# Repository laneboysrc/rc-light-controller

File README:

This project is for a light controller for Radio Controlled cars. 

See http://laneboysrc.blogspot.sg/2012/07/diy-car-light-controller-for-3-channel.html
for details.

It makes uses of a PIC 16F628A microcontroller. Firmware and schematics in
Eagle format are included.

To compile you need:
- GNU Make
- gputils (Version 1.0.0; http://gputils.sourceforge.net/)

Also heck out http://laneboysrc.blogspot.sg/2012/12/pre-processor-for-diy-rc-light.html

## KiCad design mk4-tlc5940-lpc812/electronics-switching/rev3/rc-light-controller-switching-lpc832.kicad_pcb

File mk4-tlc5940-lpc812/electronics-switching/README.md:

# Mk4S - light controller with pin headers and 9 switching outputs

This is a new variant of the DIY RC Light Controller Mk4.
It has 9 (Mosfet) switched outputs on standard 2.54 mm pin headers, 8 of them with two connections and one of them with 1 connection.

We are using the TSSOP-20 package of the LPC812 as it is easier to source (as of 2020) than the TSSOP-16 version, and we have plenty of space.

# 2021 electronics shortage

As of early 2021, many electronics components are out of stock due to global semiconductor shortage. This affects also the LPC812 microcontroller.

As of April 2021 a similar microcontroller from NXP, the LPC832M101FDH20 was still in stock at some distributors (but stocks declined towards mid of April rapidly). We prepared a new circuit board for the LPC832, and also ported the firmware.

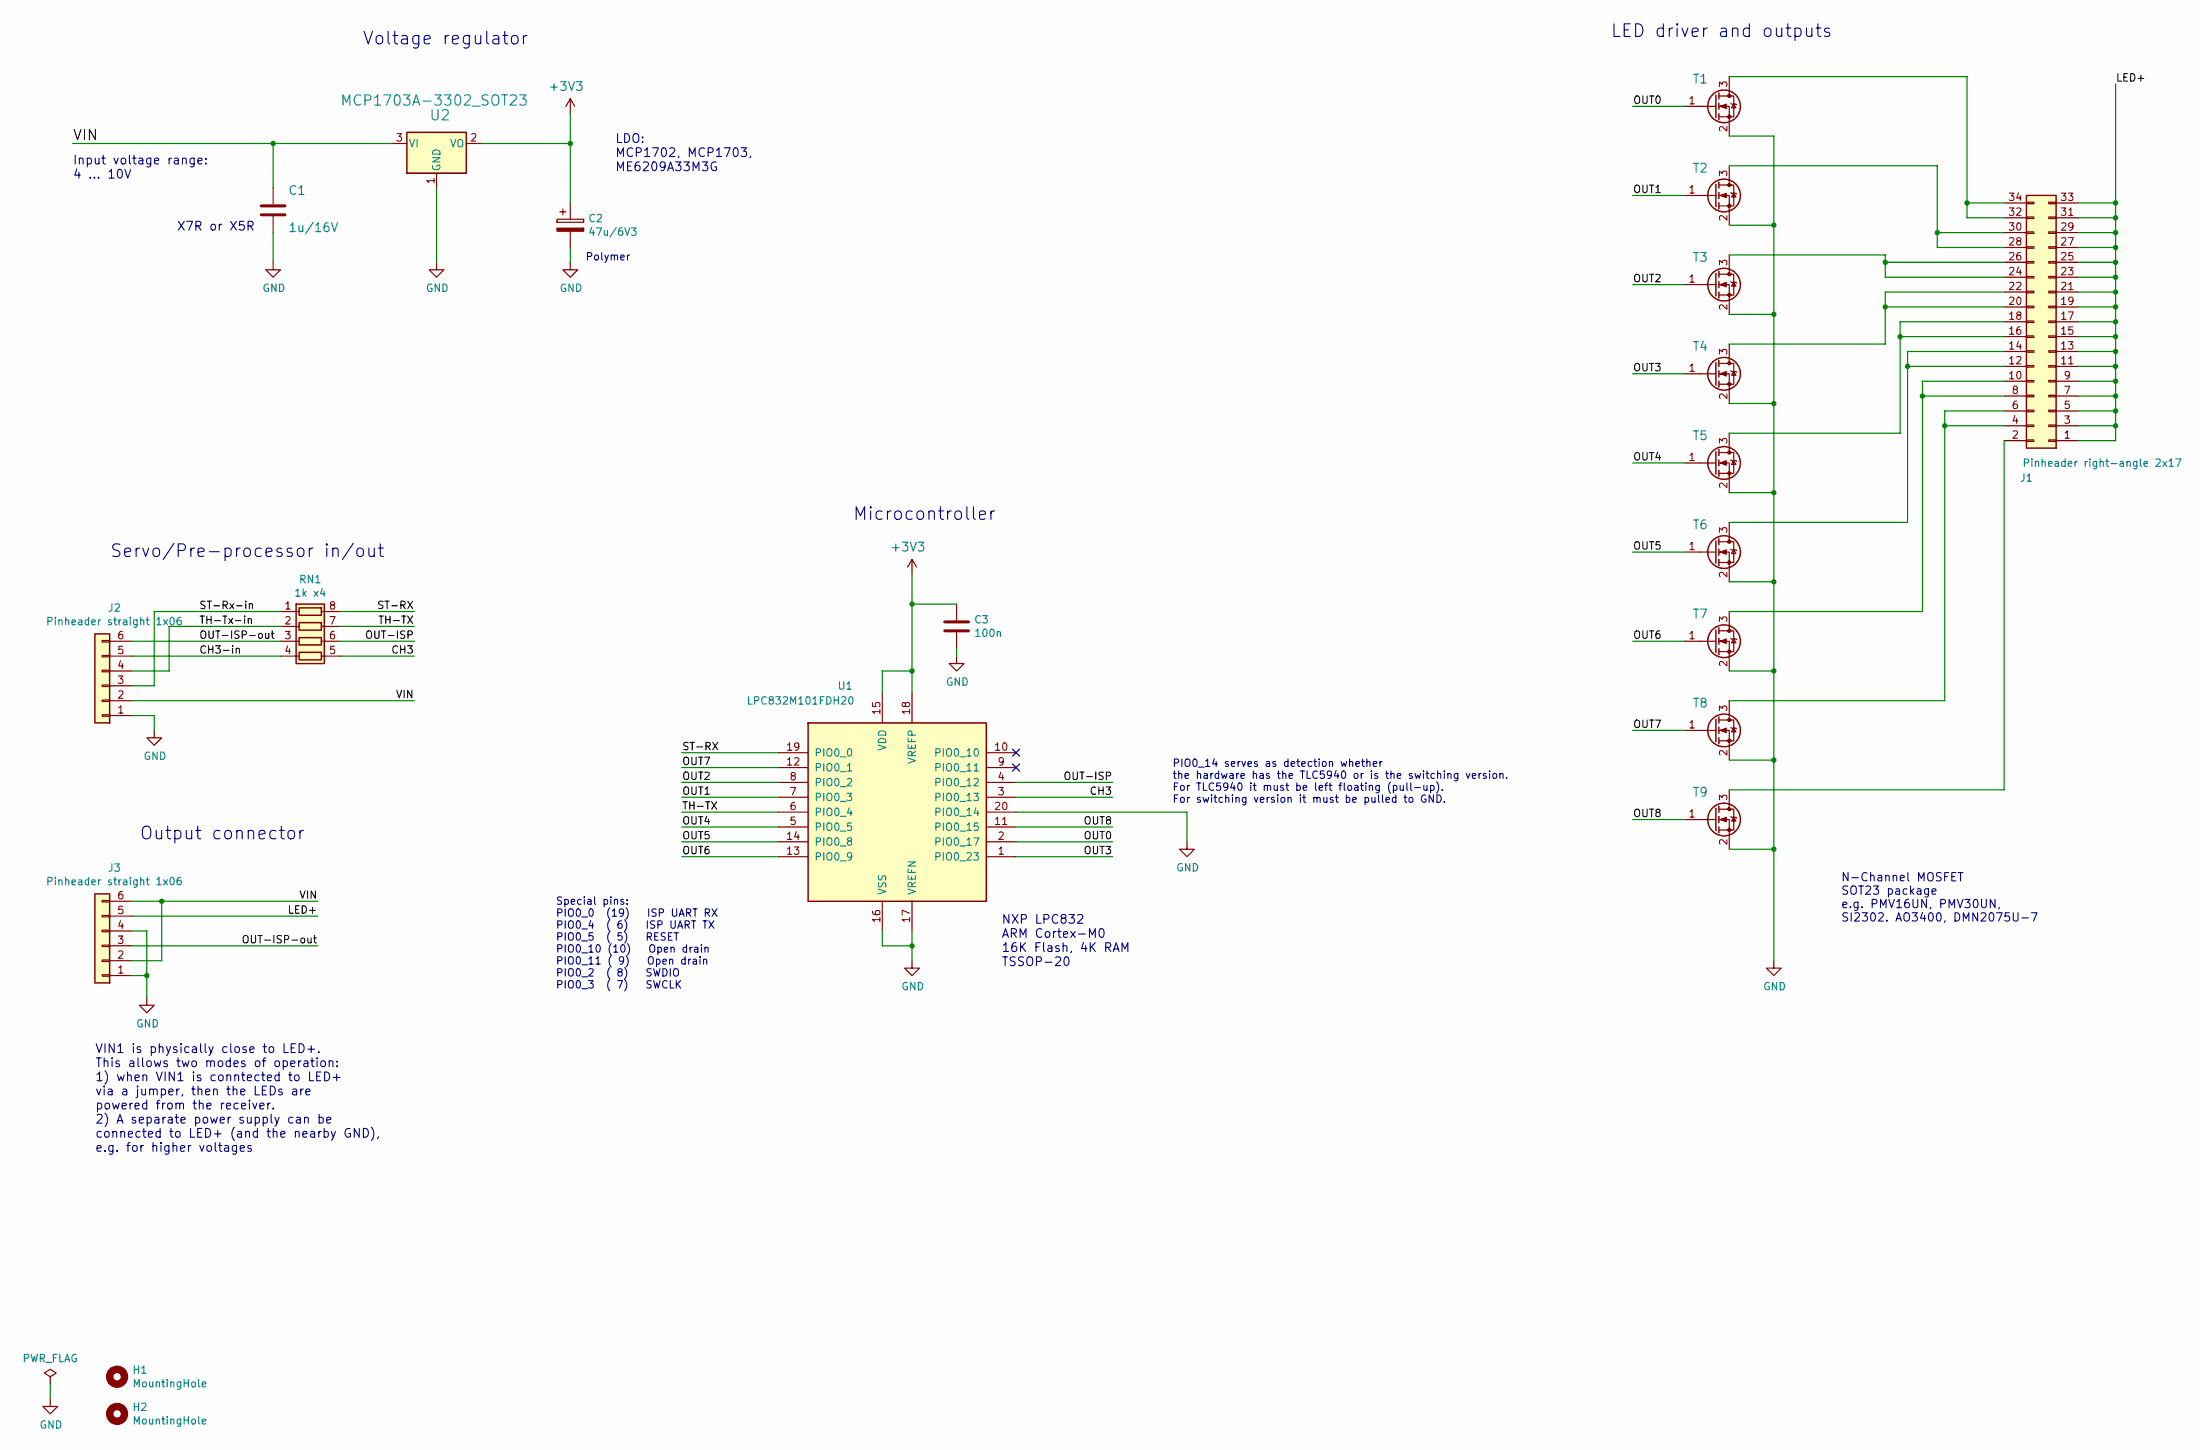
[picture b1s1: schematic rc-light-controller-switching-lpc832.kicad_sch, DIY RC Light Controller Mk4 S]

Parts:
C1: 1u/16V; C_0805_2012Metric
C2: 47u/6V3; C_0805_2012Metric
C3: 100n; C_0603_1608Metric
H1, H2: MountingHole; MountingHole_2.2mm_M2_ISO14580
J1: Pinheader right-angle 2x17; PinHeader_2x17_P2.54mm_Horizontal
J2, J3: Pinheader straight 1x06; PinHeader_1x06_P2.54mm_Flat
RN1: 1k x4; R_Array_Convex_4x0603
T1, T2, T3, T4, T5, T6, T7, T8, T9: PMV30UN; SOT-23
U1: LPC832M101FDH20; TSSOP-20_4.4x6.5mm_P0.65mm
U2: MCP1703A-3302_SOT23; SOT-23W

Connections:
+3V3: C2.1, C3.1, U1.15 (VDD), U1.18 (VREFP), U2.2 (VO)
/CH3: RN1.5 (R4.2), U1.3 (PIO0_13)
/CH3-in: J2.5, RN1.4 (R4.1)
/LED+: J1.1, J1.3, J1.5, J1.7, J1.9, J1.11, J1.13, J1.15, J1.17, J1.19, J1.21, J1.23, J1.25, J1.27, J1.29, J1.31, J1.33, J3.5
/OUT0: T1.1 (G), U1.2 (PIO0_17)
/OUT1: T2.1 (G), U1.7 (PIO0_3)
/OUT2: T3.1 (G), U1.8 (PIO0_2)
/OUT3: T4.1 (G), U1.1 (PIO0_23)
/OUT4: T5.1 (G), U1.5 (PIO0_5)
/OUT5: T6.1 (G), U1.14 (PIO0_8)
/OUT6: T7.1 (G), U1.13 (PIO0_9)
/OUT7: T8.1 (G), U1.12 (PIO0_1)
/OUT8: T9.1 (G), U1.11 (PIO0_15)
/OUT-ISP: RN1.6 (R3.2), U1.4 (PIO0_12)
/OUT-ISP-out: J2.6, J3.3, RN1.3 (R3.1)
/ST-RX: RN1.8 (R1.2), U1.19 (PIO0_0)
/ST-Rx-in: J2.3, RN1.1 (R1.1)
/TH-TX: RN1.7 (R2.2), U1.6 (PIO0_4)
/TH-Tx-in: J2.4, RN1.2 (R2.1)
/VIN: C1.1, J2.2, J3.2, J3.6, U2.3 (VI)
GND: C1.2, C2.2, C3.2, J2.1, J3.1, J3.4, T1.2 (S), T2.2 (S), T3.2 (S), T4.2 (S), T5.2 (S), T6.2 (S), T7.2 (S), T8.2 (S), T9.2 (S), U1.16 (VSS), U1.17 (VREFN), U1.20 (PIO0_14), U2.1 (GND)
unnamed: J1.2, T9.3 (D)
unnamed: J1.4, J1.6, T8.3 (D)
unnamed: J1.8, J1.10, T7.3 (D)
unnamed: J1.12, J1.14, T6.3 (D)
unnamed: J1.16, J1.18, T5.3 (D)
unnamed: J1.20, J1.22, T4.3 (D)
unnamed: J1.24, J1.26, T3.3 (D)
unnamed: J1.28, J1.30, T2.3 (D)
unnamed: J1.32, J1.34, T1.3 (D)

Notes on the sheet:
N-Channel MOSFET SOT23 package e.g. PMV16UN, PMV30UN, SI2302. AO3400, DMN2075U-7
PIO0_14 serves as detection whether the hardware has the TLC5940 or is the switching version. For TLC5940 it must be left floating (pull-up). For switching version it must be pulled to GND.
Polymer
Microcontroller
X7R or X5R
Input voltage range: 4 ... 10V
LED driver and outputs
Special pins: PIO0_0 (19) ISP UART RX PIO0_4 ( 6) ISP UART TX PIO0_5 ( 5) RESET PIO0_10 (10) Open drain PIO0_11 ( 9) Open drain PIO0_2 ( 8) SWDIO PIO0_3 ( 7) SWCLK
Servo/Pre-processor in/out
Voltage regulator
VIN1 is physically close to LED+. This allows two modes of operation: 1) when VIN1 is conntected to LED+ via a jumper, then the LEDs are powered from the receiver. 2) A separate power supply can be connected to LED+ (and the nearby GND), e.g. for higher voltages
LDO: MCP1702, MCP1703, ME6209A33M3G
Output connector
NXP LPC832 ARM Cortex-M0 16K Flash, 4K RAM TSSOP-20

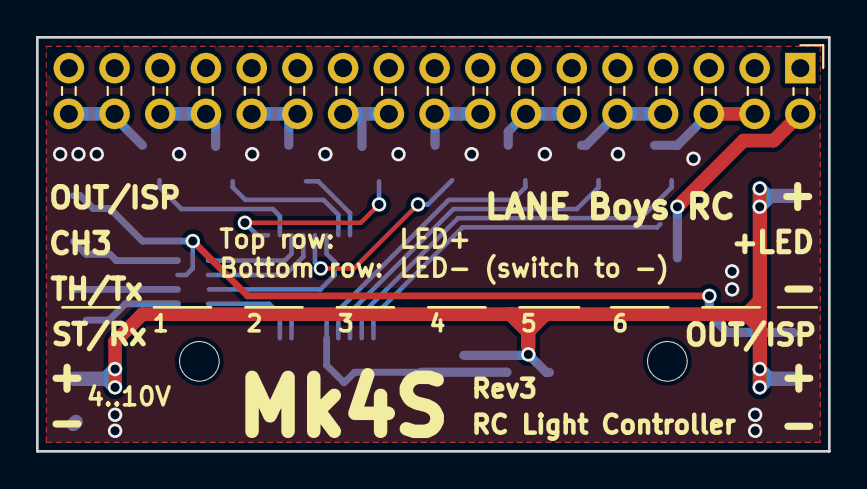
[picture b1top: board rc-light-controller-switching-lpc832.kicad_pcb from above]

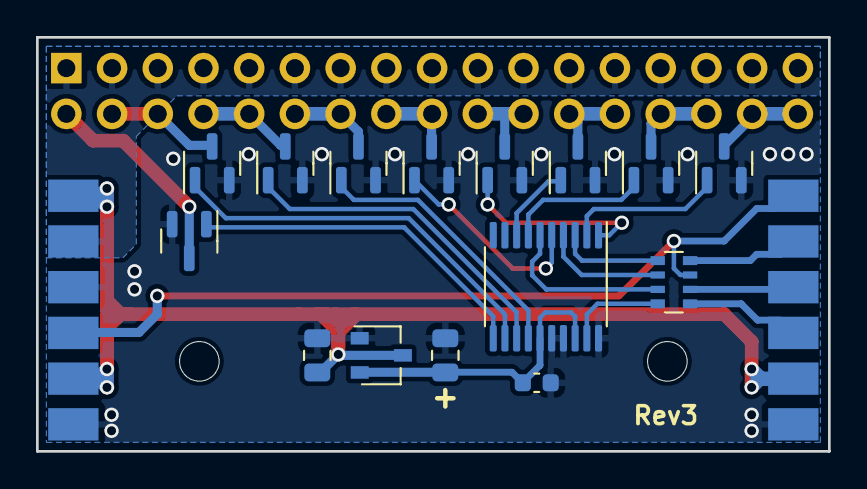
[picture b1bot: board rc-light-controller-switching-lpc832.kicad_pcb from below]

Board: 2 copper layers, 44.0 x 23.0 mm, 20 parts (17 on the bottom side), 30 nets.

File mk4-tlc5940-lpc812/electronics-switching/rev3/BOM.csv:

Reference, Quantity, Value, Footprint, Datasheet
C1 ,1,"1u/16V","Capacitor_SMD:C_0805_2012Metric",""
C2 ,1,"47u/6V3","Capacitor_SMD:C_0805_2012Metric","https://www.vishay.com/doc?40189"
C3 ,1,"100n","Capacitor_SMD:C_0603_1608Metric","~"
H1 H2 ,2,"MountingHole","MountingHole:MountingHole_2.2mm_M2_ISO14580","~"
J1 ,1,"Pinheader right-angle 2x17","Connector_PinHeader_2.54mm:PinHeader_2x17_P2.54mm_Horizontal","~"
J2 J3 ,2,"Pinheader straight 1x06","rc-light-controller-tlc5940-lpc812:PinHeader_1x06_P2.54mm_Flat","~"
RN1 ,1,"1k x4","Resistor_SMD:R_Array_Convex_4x0603","https://datasheet.lcsc.com/szlcsc/1810311812_UNI-ROYAL-Uniro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"
T1 T2 T3 T4 T5 T6 T7 T9 T8 ,9,"PMV30UN","Package_TO_SOT_SMD:SOT-23","https://assets.nexperia.com/documents/data-sheet/PMV30UN.pdf"
U1 ,1,"LPC832M101FDH20","Package_SO:TSSOP-20_4.4x6.5mm_P0.65mm","http://www.nxp.com/documents/data_sheet/LPC83X.pdf"
U2 ,1,"MCP1703A-3302","Package_TO_SOT_SMD:SOT-23W",""

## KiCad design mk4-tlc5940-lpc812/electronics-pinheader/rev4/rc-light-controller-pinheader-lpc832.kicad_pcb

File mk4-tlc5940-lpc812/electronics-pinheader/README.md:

# Mk4P - light controller with pin headers

This is a variant of the DIY RC Light Controller Mk4 where all outputs are available on a standard 2.54 mm pin header.

We are using a microcontroller from NXP: LPC824M101FDH20 (or LPC832M101FDH20) in TSSOP-20 package.

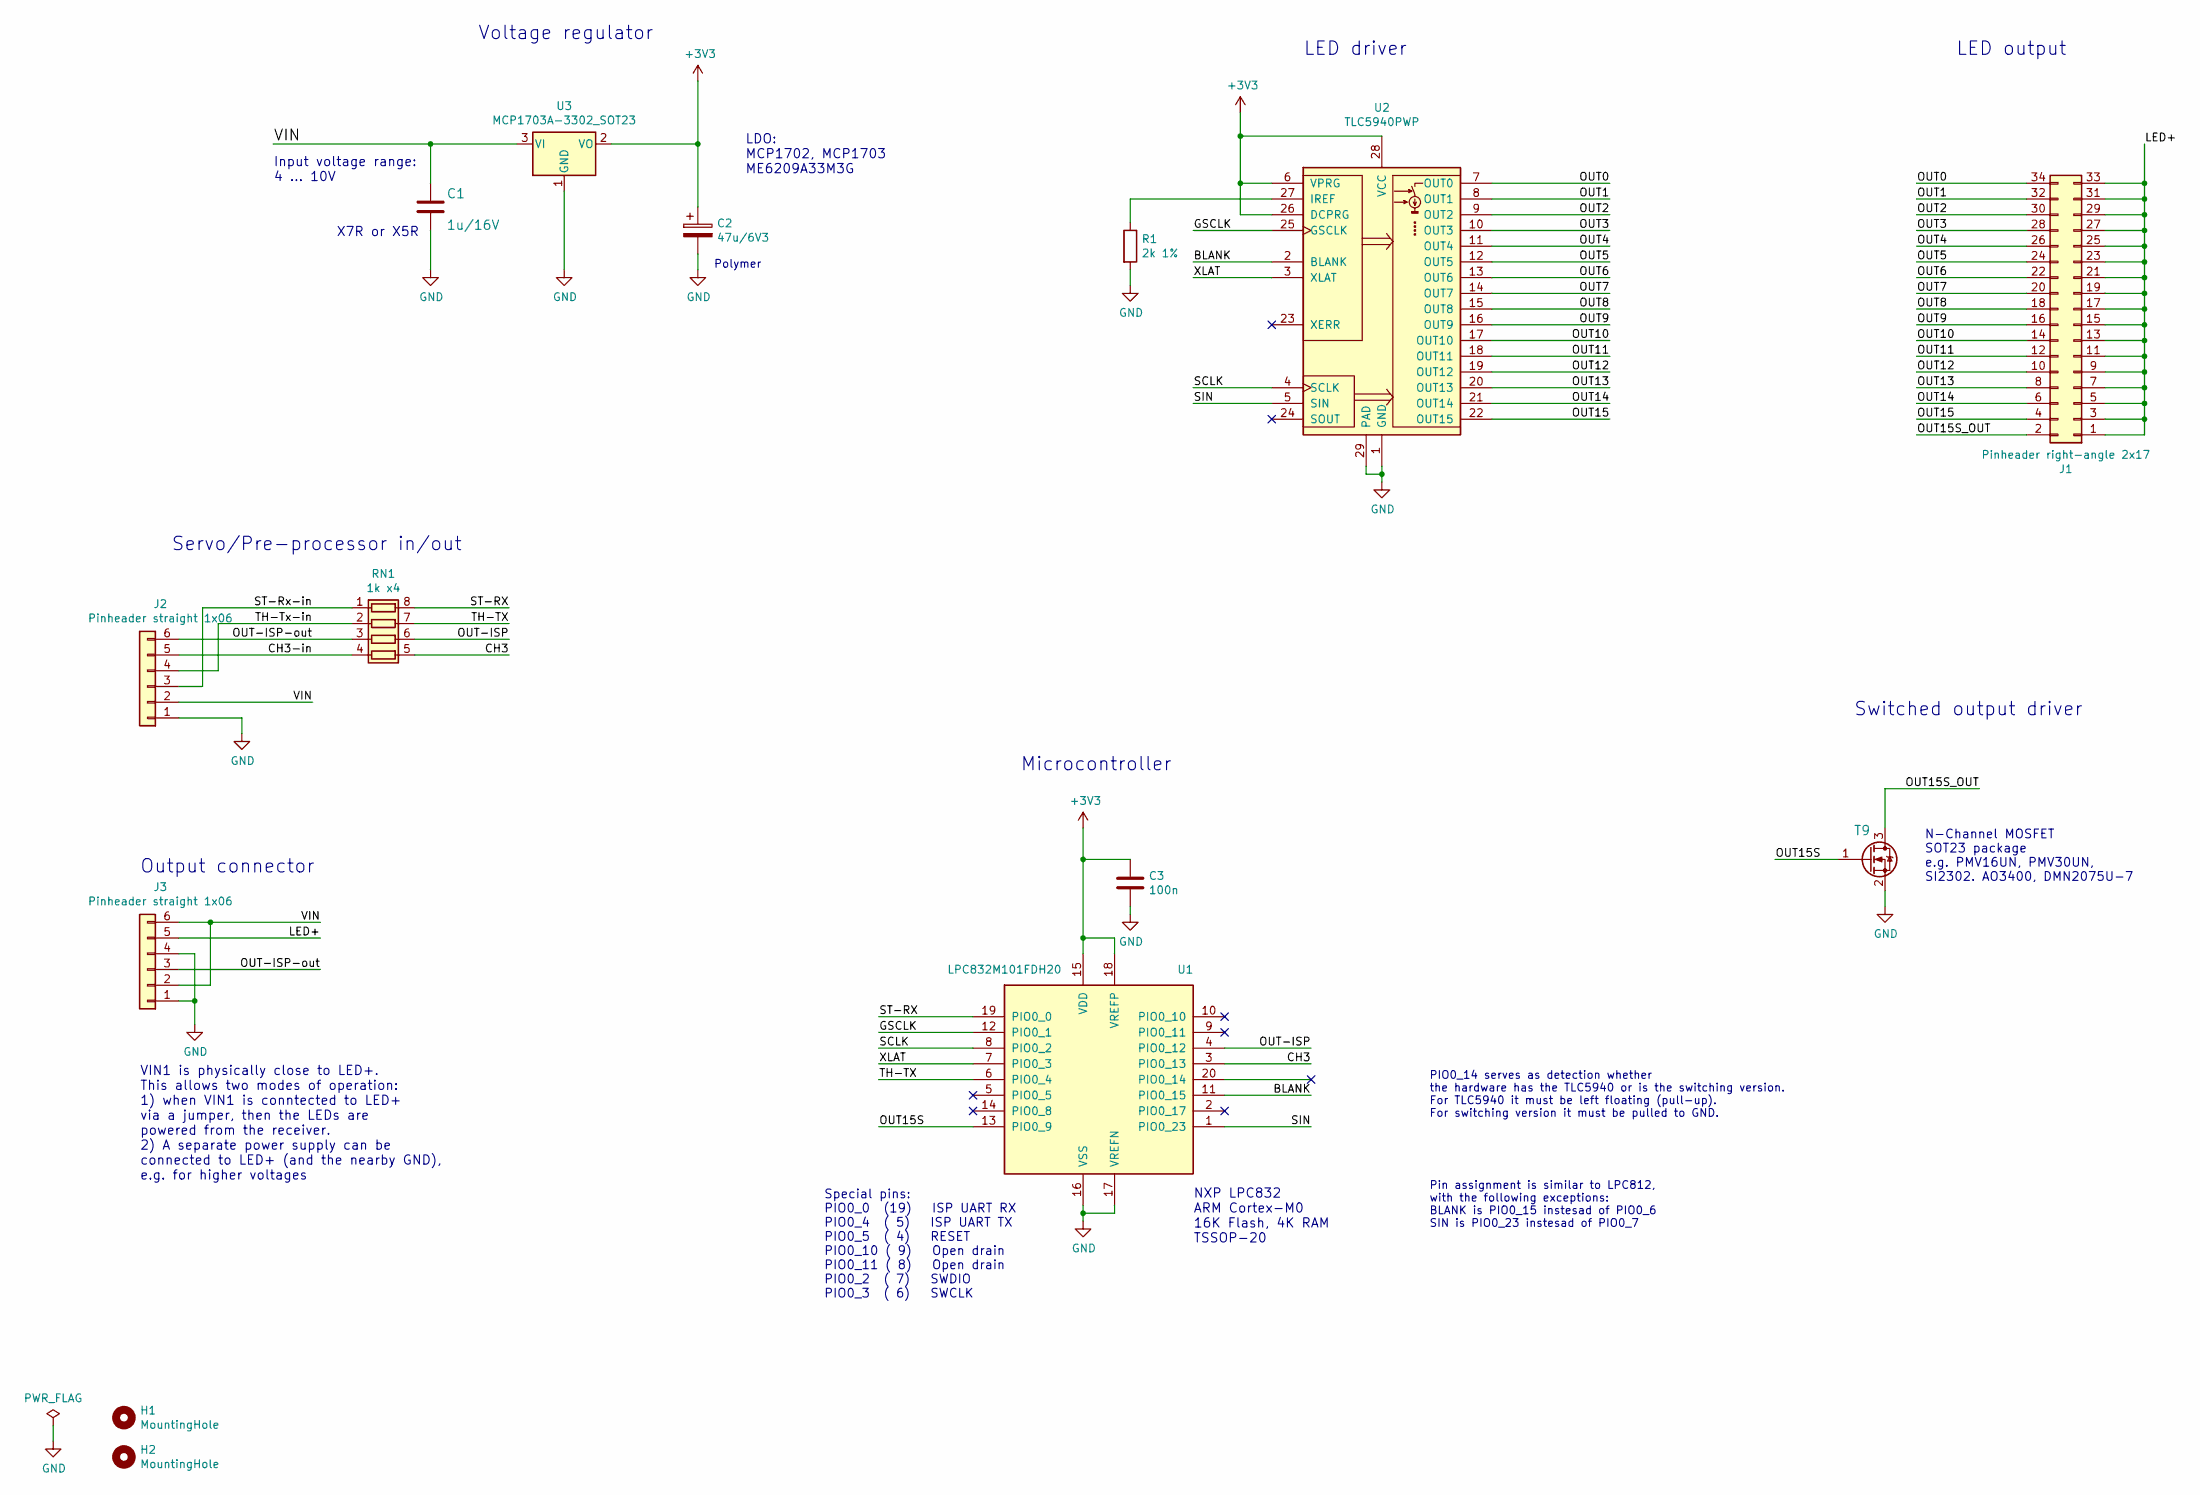
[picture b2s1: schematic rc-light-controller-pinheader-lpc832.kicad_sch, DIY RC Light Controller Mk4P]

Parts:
C1: 1u/16V; C_0805_2012Metric
C2: 47u/6V3; C_0805_2012Metric
C3: 100n; C_0603_1608Metric
H1, H2: MountingHole; MountingHole_2.2mm_M2_ISO14580
J1: Pinheader right-angle 2x17; PinHeader_2x17_P2.54mm_Horizontal
J2, J3: Pinheader straight 1x06; PinHeader_1x06_P2.54mm_Flat
R1: 2k 1%; R_0603_1608Metric
RN1: 1k x4; R_Array_Convex_4x0603
T9: PMV30UN; SOT-23
U1: LPC832M101FDH20; TSSOP-20_4.4x6.5mm_P0.65mm
U2: TLC5940PWP; SOP65P640X120-29N
U3: MCP1703A-3302_SOT23; SOT-23W

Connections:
+3V3: C2.1, C3.1, U1.15 (VDD), U1.18 (VREFP), U2.6 (VPRG), U2.26 (DCPRG), U2.28 (VCC), U3.2 (VO)
/BLANK: U1.11 (PIO0_15), U2.2 (BLANK)
/CH3: RN1.5 (R4.2), U1.3 (PIO0_13)
/CH3-in: J2.5, RN1.4 (R4.1)
/GSCLK: U1.12 (PIO0_1), U2.25 (GSCLK)
/LED+: J1.1, J1.3, J1.5, J1.7, J1.9, J1.11, J1.13, J1.15, J1.17, J1.19, J1.21, J1.23, J1.25, J1.27, J1.29, J1.31, J1.33, J3.5
/OUT0: J1.34, U2.7 (OUT0)
/OUT1: J1.32, U2.8 (OUT1)
/OUT2: J1.30, U2.9 (OUT2)
/OUT3: J1.28, U2.10 (OUT3)
/OUT4: J1.26, U2.11 (OUT4)
/OUT5: J1.24, U2.12 (OUT5)
/OUT6: J1.22, U2.13 (OUT6)
/OUT7: J1.20, U2.14 (OUT7)
/OUT8: J1.18, U2.15 (OUT8)
/OUT9: J1.16, U2.16 (OUT9)
/OUT10: J1.14, U2.17 (OUT10)
/OUT11: J1.12, U2.18 (OUT11)
/OUT12: J1.10, U2.19 (OUT12)
/OUT13: J1.8, U2.20 (OUT13)
/OUT14: J1.6, U2.21 (OUT14)
/OUT15: J1.4, U2.22 (OUT15)
/OUT15S: T9.1 (G), U1.13 (PIO0_9)
/OUT15S_OUT: J1.2, T9.3 (D)
/OUT-ISP: RN1.6 (R3.2), U1.4 (PIO0_12)
/OUT-ISP-out: J2.6, J3.3, RN1.3 (R3.1)
/SCLK: U1.8 (PIO0_2), U2.4 (SCLK)
/SIN: U1.1 (PIO0_23), U2.5 (SIN)
/ST-RX: RN1.8 (R1.2), U1.19 (PIO0_0)
/ST-Rx-in: J2.3, RN1.1 (R1.1)
/TH-TX: RN1.7 (R2.2), U1.6 (PIO0_4)
/TH-Tx-in: J2.4, RN1.2 (R2.1)
/VIN: C1.1, J2.2, J3.2, J3.6, U3.3 (VI)
/XLAT: U1.7 (PIO0_3), U2.3 (XLAT)
GND: C1.2, C2.2, C3.2, J2.1, J3.1, J3.4, R1.2, T9.2 (S), U1.16 (VSS), U1.17 (VREFN), U2.1 (GND), U2.29 (PAD), U3.1 (GND)
unnamed: R1.1, U2.27 (IREF)

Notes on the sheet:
N-Channel MOSFET SOT23 package e.g. PMV16UN, PMV30UN, SI2302. AO3400, DMN2075U-7
LED driver
Microcontroller
LED output
Special pins: PIO0_0 (19) ISP UART RX PIO0_4 ( 5) ISP UART TX PIO0_5 ( 4) RESET PIO0_10 ( 9) Open drain PIO0_11 ( 8) Open drain PIO0_2 ( 7) SWDIO PIO0_3 ( 6) SWCLK
LDO: MCP1702, MCP1703 ME6209A33M3G
X7R or X5R
PIO0_14 serves as detection whether the hardware has the TLC5940 or is the switching version. For TLC5940 it must be left floating (pull-up). For switching version it must be pulled to GND.
Polymer
Pin assignment is similar to LPC812, with the following exceptions: BLANK is PIO0_15 instesad of PIO0_6 SIN is PIO0_23 instesad of PIO0_7
VIN1 is physically close to LED+. This allows two modes of operation: 1) when VIN1 is conntected to LED+ via a jumper, then the LEDs are powered from the receiver. 2) A separate power supply can be connected to LED+ (and the nearby GND), e.g. for higher voltages
Voltage regulator
Servo/Pre-processor in/out
Switched output driver
NXP LPC832 ARM Cortex-M0 16K Flash, 4K RAM TSSOP-20
Output connector
Input voltage range: 4 ... 10V

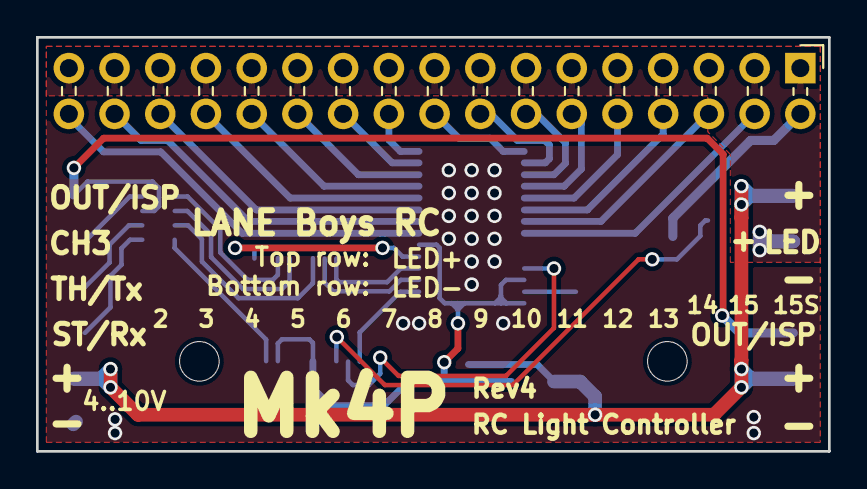
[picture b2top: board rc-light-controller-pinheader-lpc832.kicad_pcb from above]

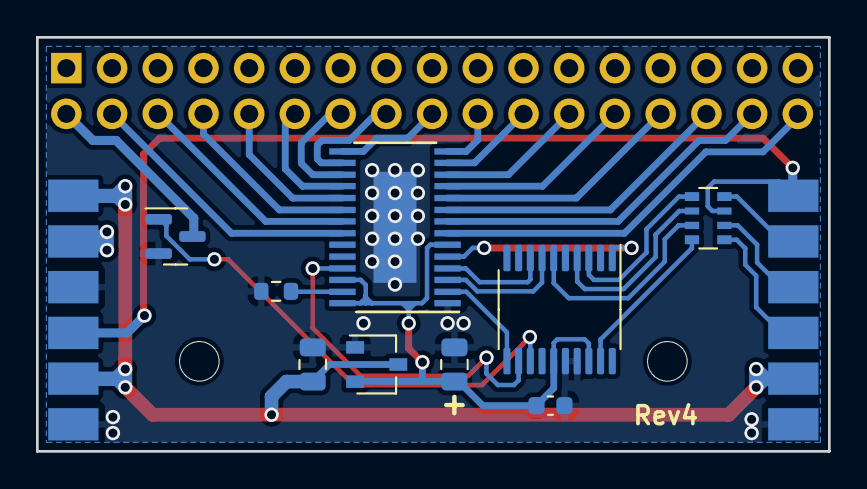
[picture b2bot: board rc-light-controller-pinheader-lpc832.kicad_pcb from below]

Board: 2 copper layers, 44.0 x 23.0 mm, 14 parts (11 on the bottom side), 36 nets.

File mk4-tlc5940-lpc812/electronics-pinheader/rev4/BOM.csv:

Reference, Quantity, Value, Footprint, Datasheet
C1 ,1,1u/16V,Capacitor_SMD:C_0805_2012Metric,
C2 ,1,47u/6V3,Capacitor_SMD:C_0805_2012Metric,https://www.vishay.com/doc?40189
C3 ,1,100n,Capacitor_SMD:C_0603_1608Metric,~
H1 H2 ,2,MountingHole,MountingHole:MountingHole_2.2mm_M2_ISO14580,~
J1 ,1,Pinheader right-angle 2x17,Connector_PinHeader_2.54mm:PinHeader_2x17_P2.54mm_Horizontal,~
J2 J3 ,2,Pinheader straight 1x06,rc-light-controller-tlc5940-lpc812:PinHeader_1x06_P2.54mm_Flat,~
R1 ,1,2k 1%,Resistor_SMD:R_0603_1608Metric,~
RN1 ,1,1k x4,Resistor_SMD:R_Array_Convex_4x0603,https://datasheet.lcsc.com/szlcsc/1810311812_UNI-ROYAL-Uniro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
T9 ,1,PMV30UN,Package_TO_SOT_SMD:SOT-23,https://assets.nexperia.com/documents/data-sheet/PMV30UN.pdf
U1 ,1,LPC832M101FDH20,Package_SO:TSSOP-20_4.4x6.5mm_P0.65mm,http://www.nxp.com/documents/data_sheet/LPC81XM.pdf
U2 ,1,TLC5940PWPR,rc-light-controller-tlc5940-lpc812:SOP65P640X120-29N,http://www.ti.com/lit/ds/symlink/tlc5940.pdf
U3 ,1,MCP1703A-3302_SOT23,Package_TO_SOT_SMD:SOT-23W,http://ww1.microchip.com/downloads/en/DeviceDoc/20005122B.pdf

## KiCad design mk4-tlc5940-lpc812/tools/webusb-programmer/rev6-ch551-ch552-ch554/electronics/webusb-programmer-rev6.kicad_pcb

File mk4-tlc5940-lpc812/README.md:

# Light controller MK4 TLC5940 LPC812 / LPC832

Usually light controller users can use the on-line Configurator at https://laneboysrc.github.io/rc-light-controller/ to adjust all settings to their need and use the WebUSB programmer to flash the resulting firmware.

---

For configuring the light controller offline, please download **[mk4-download-me.zip](mk4-download-me.zip)**.

This archive contains the configuration tool *configurator.html*. Open this file in your Web browser.
**configurator.html has the firmware already embedded**, just set the options you want and click on the *Save firmware image...* button.

The configured firmware image *light_controller.hex* will be stored in the *Download* folder of your web browser.

If you don't have the WebUSB programmer, you can use the LPC81x-ISP tool included in the archive to flash the firmware. You need a USB-to-serial adapter to connect your PC to the light controller.

Wire-up the USB-to-serial adapter as follows:

---

In the rare event you want to modify the firmware, please consult [README.md](firmware/README.md) for build instructions.

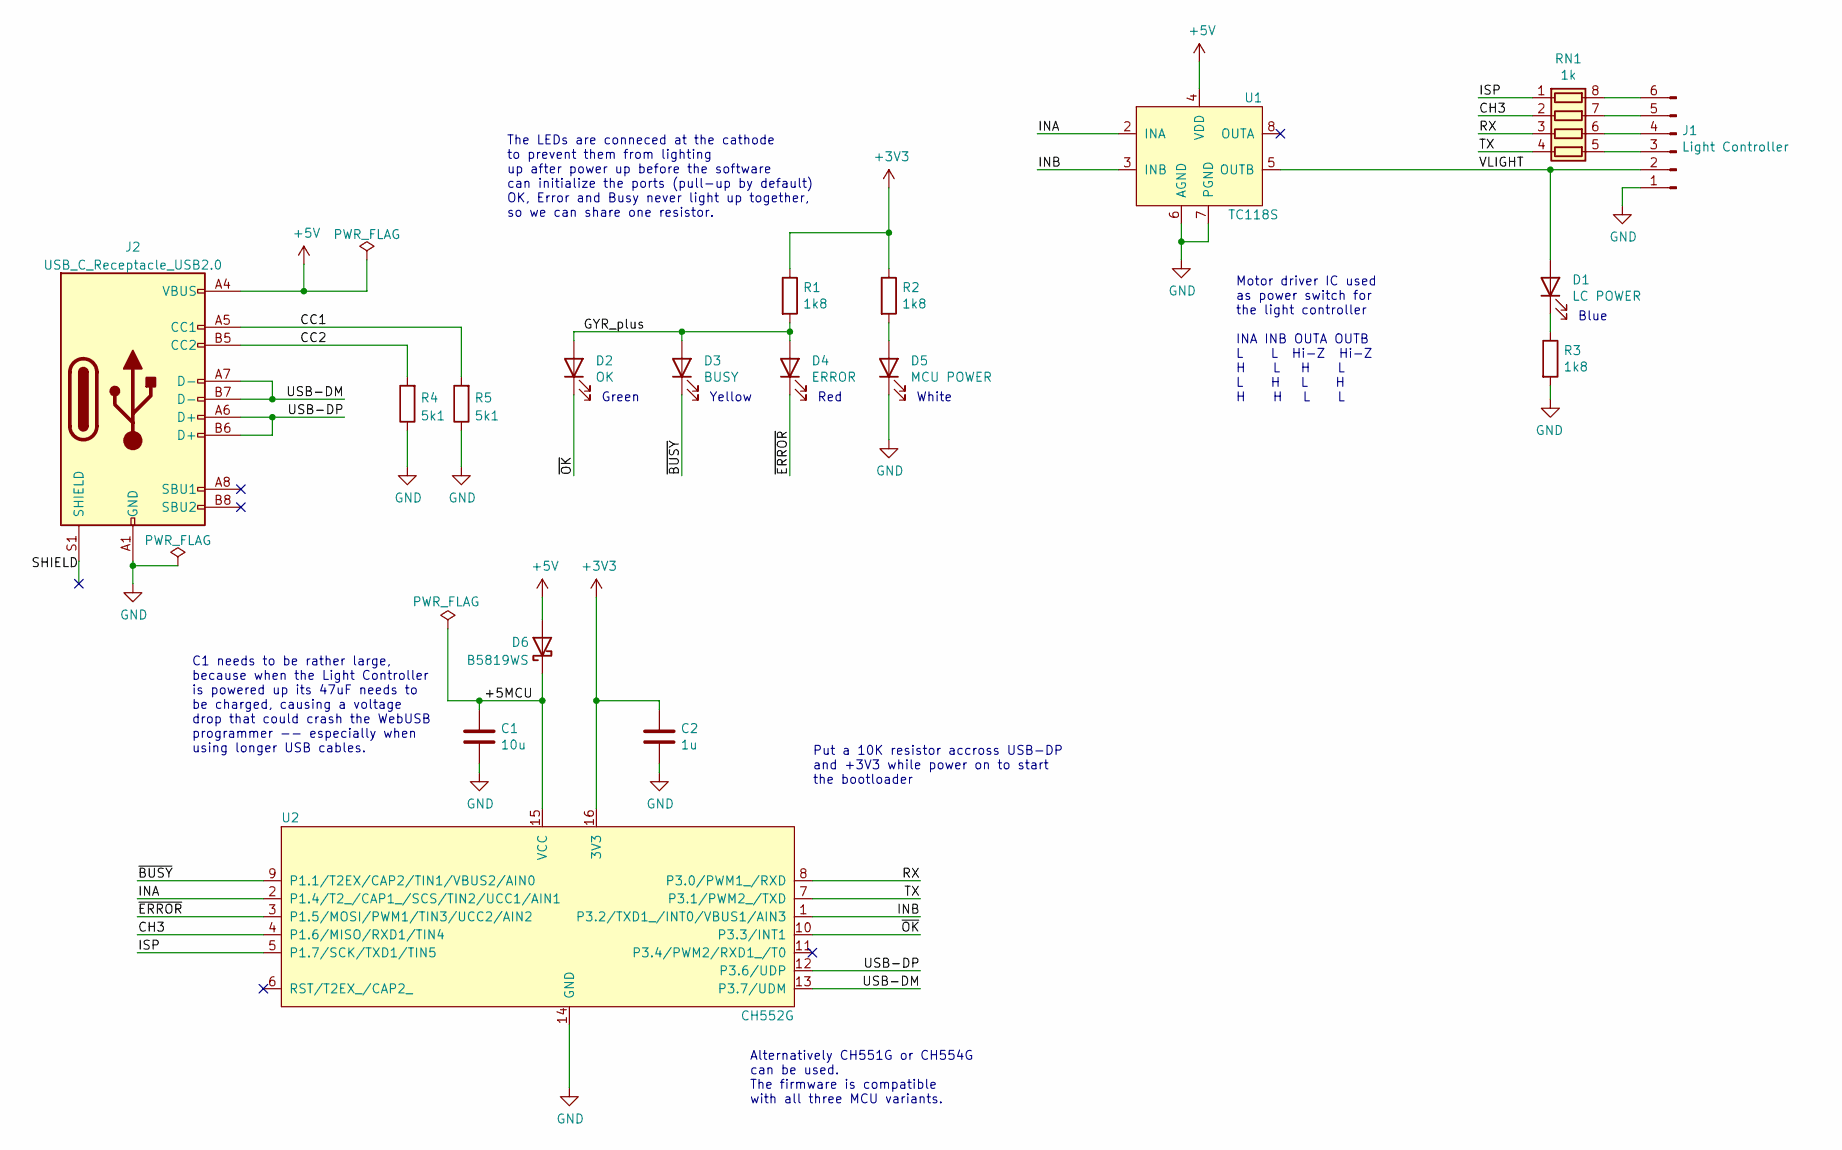
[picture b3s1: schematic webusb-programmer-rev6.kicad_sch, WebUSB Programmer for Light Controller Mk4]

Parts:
C1: 10u; C_0603_1608Metric
C2: 1u; C_0603_1608Metric
D1: LC POWER; LED_0805_2012Metric_see_through; LCSC part number C779807
D2: OK; LED_0805_2012Metric_see_through; LCSC part number C779806
D3: BUSY; LED_0805_2012Metric_see_through; LCSC part number C779805
D4: ERROR; LED_0805_2012Metric_see_through; LCSC part number C389527
D5: MCU POWER; LED_0805_2012Metric_see_through; LCSC part number C779804
D6: B5819WS; D_SOD-123
J1: Light Controller; PinHeader_1x06_P2.54mm_Flat
J2: USB_C_Receptacle_USB2.0; USB_C_Receptacle_G-Switch_GT-USB-7010ASV
R1, R2, R3: 1k8; R_0603_1608Metric
R4, R5: 5k1; R_0603_1608Metric
RN1: 1k; R_Array_Convex_4x0603
U1: TC118S; SOP-8_3.9x4.9mm_P1.27mm; LCSC part number C88308
U2: CH552G; SO-16_3.9x9.9mm_P1.27mm; LCSC part number C111292

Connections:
+3V3: C2.1, R1.1, R2.1, U2.16 (3V3)
+5V: D6.2 (A), J2.A4 (VBUS), J2.A9 (VBUS), J2.B4 (VBUS), J2.B9 (VBUS), U1.4 (VDD)
/+5MCU: C1.1, D6.1 (K), U2.15 (VCC)
/CC1: J2.A5 (CC1), R5.2
/CC2: J2.B5 (CC2), R4.2
/CH3: RN1.2 (R2.1), U2.4 (P1.6/MISO/RXD1/TIN4)
/GYR_plus: D2.2 (A), D3.2 (A), D4.2 (A), R1.2
/INA: U1.2 (INA), U2.2 (P1.4/T2_/CAP1_/SCS/TIN2/UCC1/AIN1)
/INB: U1.3 (INB), U2.1 (P3.2/TXD1_/INT0/VBUS1/AIN3)
/ISP: RN1.1 (R1.1), U2.5 (P1.7/SCK/TXD1/TIN5)
/RX: RN1.3 (R3.1), U2.8 (P3.0/PWM1_/RXD)
/SHIELD: J2.S1 (SHIELD)
/TX: RN1.4 (R4.1), U2.7 (P3.1/PWM2_/TXD)
/USB-DM: J2.A7 (D-), J2.B7 (D-), U2.13 (P3.7/UDM)
/USB-DP: J2.A6 (D+), J2.B6 (D+), U2.12 (P3.6/UDP)
/VLIGHT: D1.2 (A), J1.2, U1.5 (OUTB)
/~BUSY: D3.1 (K), U2.9 (P1.1/T2EX/CAP2/TIN1/VBUS2/AIN0)
/~ERROR: D4.1 (K), U2.3 (P1.5/MOSI/PWM1/TIN3/UCC2/AIN2)
/~OK: D2.1 (K), U2.10 (P3.3/INT1)
GND: C1.2, C2.2, D5.1 (K), J1.1, J2.A1 (GND), J2.A12 (GND), J2.B1 (GND), J2.B12 (GND), R3.2, R4.1, R5.1, U1.6 (AGND), U1.7 (PGND), U2.14 (GND)
unnamed: D1.1 (K), R3.1
unnamed: D5.2 (A), R2.2
unnamed: J1.3, RN1.5 (R4.2)
unnamed: J1.4, RN1.6 (R3.2)
unnamed: J1.5, RN1.7 (R2.2)
unnamed: J1.6, RN1.8 (R1.2)

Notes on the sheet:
C1 needs to be rather large, because when the Light Controller is powered up its 47uF needs to be charged, causing a voltage drop that could crash the WebUSB programmer -- especially when using longer USB cables.
Red
Blue
Green
Alternatively CH551G or CH554G can be used. The firmware is compatible with all three MCU variants.
White
Put a 10K resistor accross USB-DP and +3V3 while power on to start the bootloader
Motor driver IC used as power switch for the light controller INA INB OUTA OUTB L L Hi-Z Hi-Z H L H L L H L H H H L L
The LEDs are conneced at the cathode to prevent them from lighting up after power up before the software can initialize the ports (pull-up by default) OK, Error and Busy never light up together, so we can share one resistor.
Yellow

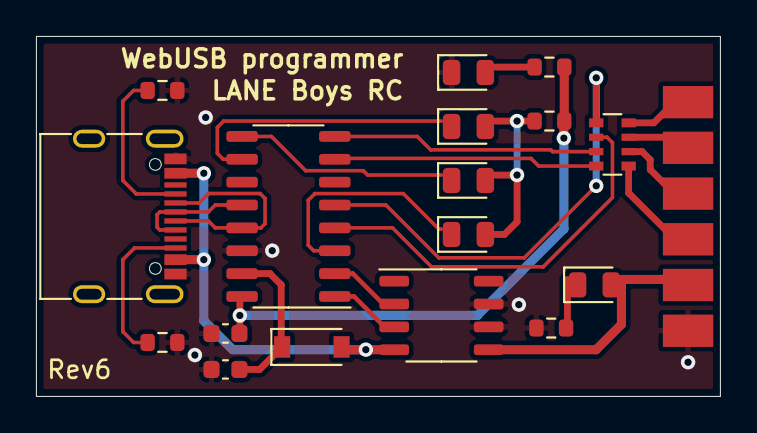
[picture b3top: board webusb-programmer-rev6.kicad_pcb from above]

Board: 2 copper layers, 38.0 x 20.0 mm, 18 parts (0 on the bottom side), 25 nets.

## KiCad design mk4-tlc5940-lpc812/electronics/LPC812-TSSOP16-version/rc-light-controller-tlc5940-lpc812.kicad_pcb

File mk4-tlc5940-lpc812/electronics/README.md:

# Mk4 - light controller with solder pads

This is the original version of the Mk4 light controller.
Multiple PCB versions are available for different microcontrollers.

The LPC812-TSSOP16 version is the original design.

pcb-size-27x20 uses the LPC812-TSSOP16 and was created to get around the minimum assembly width requirement for 3rd party manufacture. Not recommended.

The LPC812-XSON16 version uses a tiny case for the microcontroller, which is extremely difficult to work with unless you have professional equipment.

The LPC812-TSSOP20 was never built and tested.

The LPC832-TSSOP20 version is not tested yet, but most likely will work as we successfully ported the Mk4P (basically same schematics) already to the LPC832.

Background info: we ported to the different microcontroller variants to get around the global chip shortage in 2020/2021.

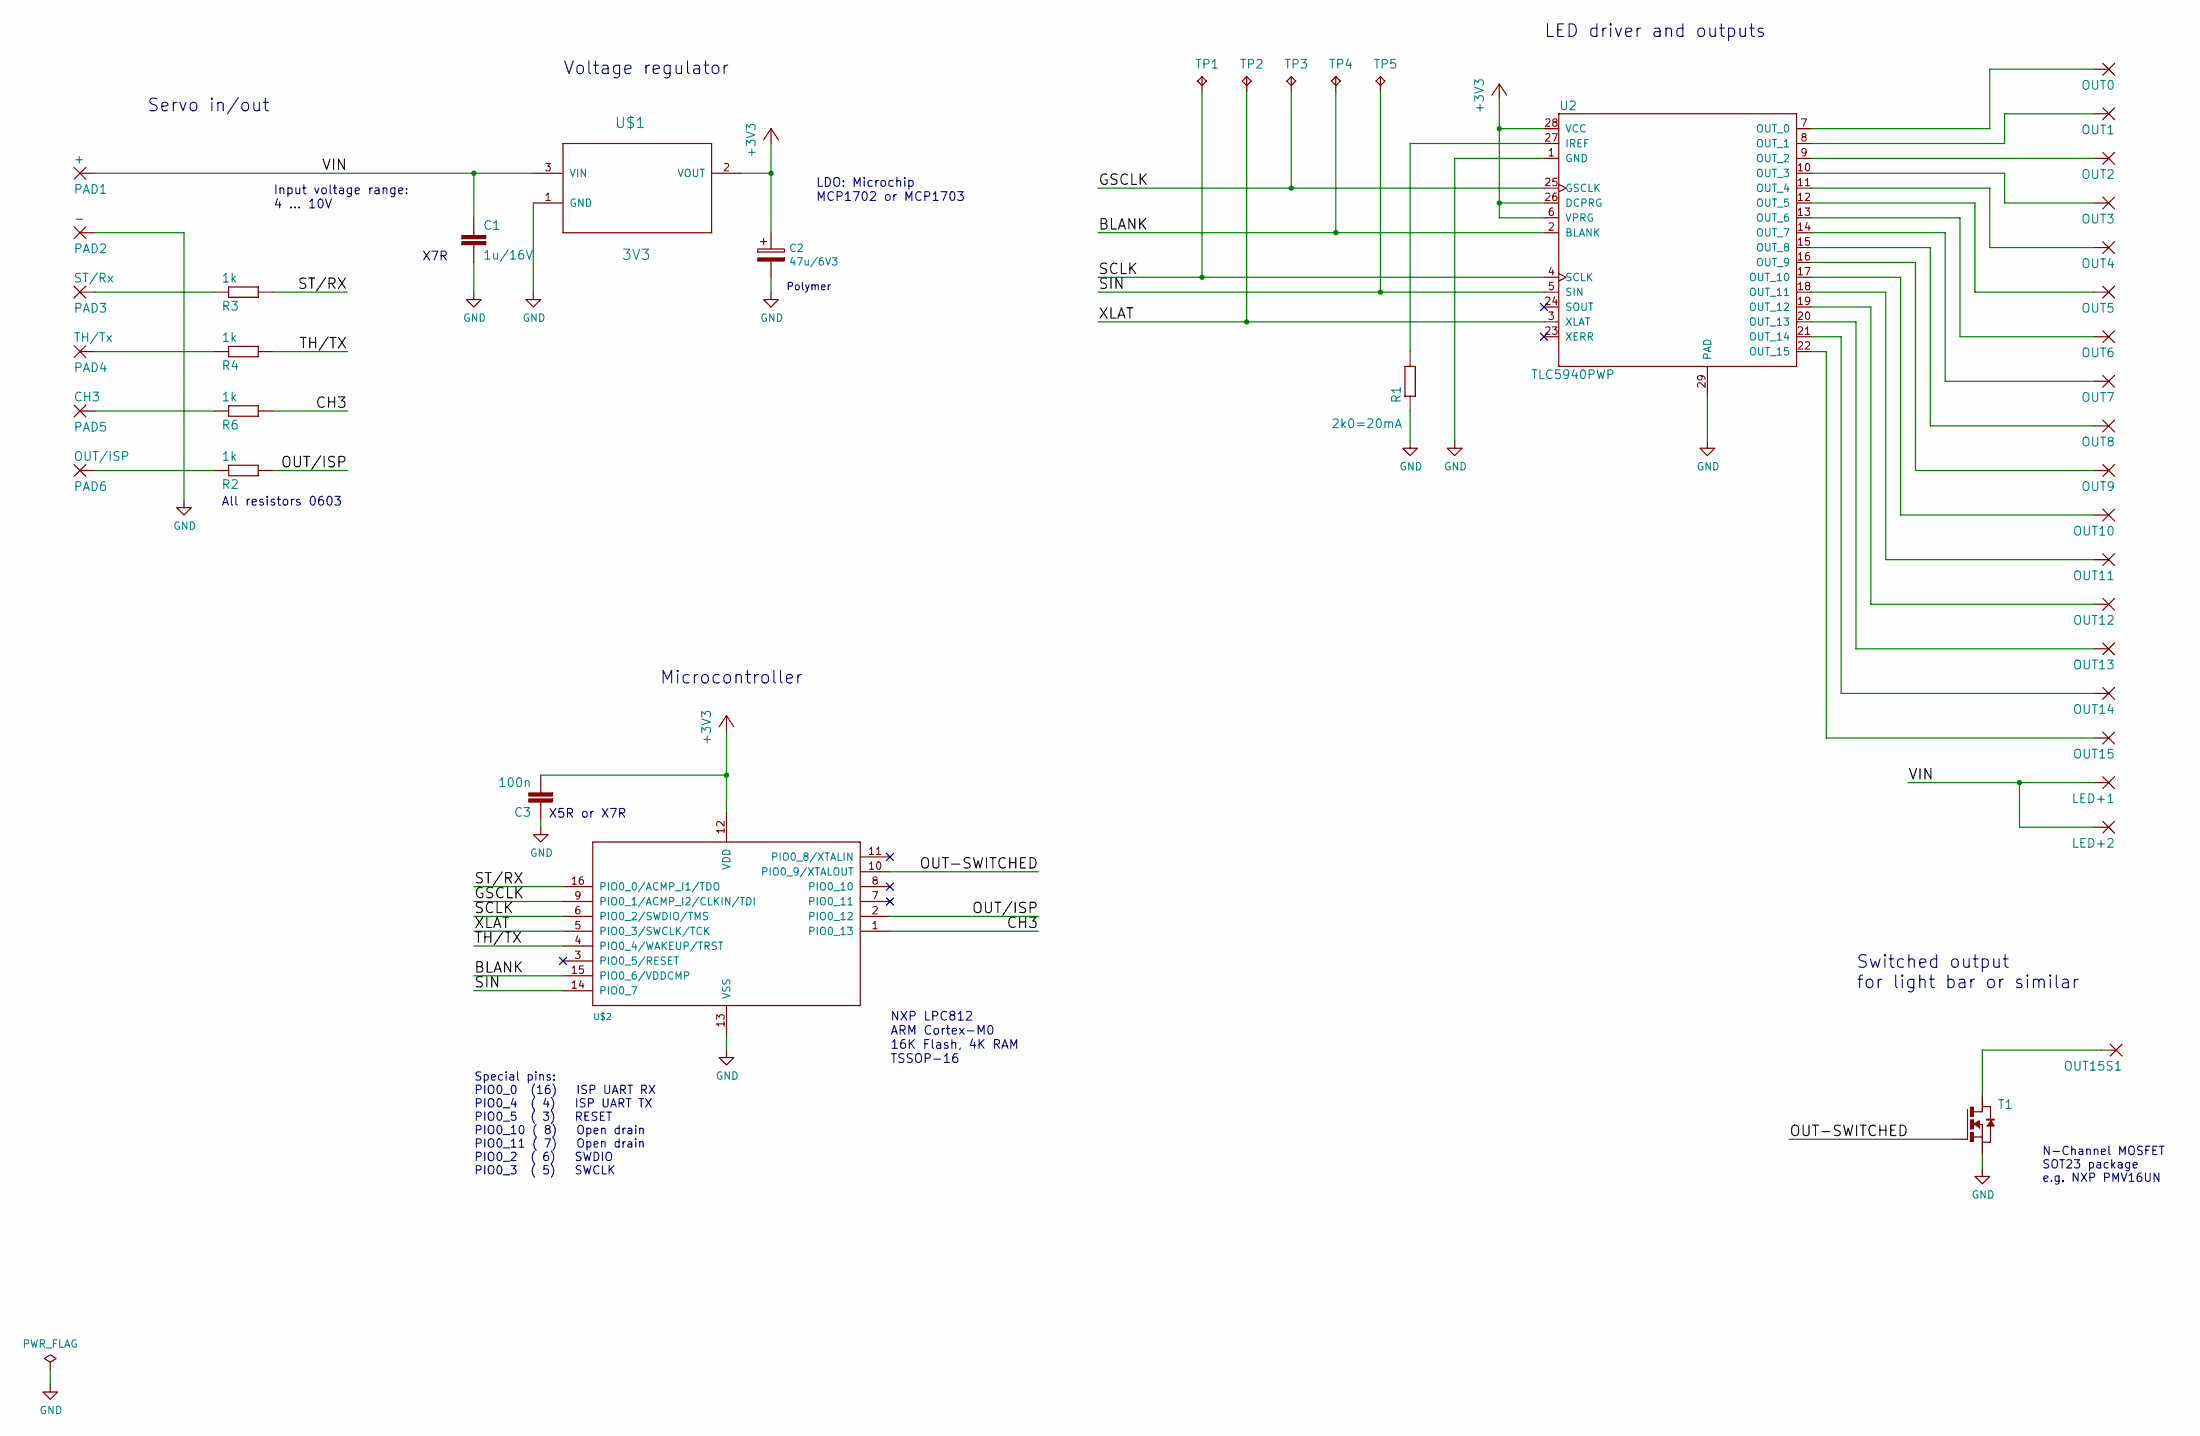
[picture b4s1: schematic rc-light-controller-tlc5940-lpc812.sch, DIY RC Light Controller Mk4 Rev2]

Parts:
C1: 1u/16V; C_0805_2012Metric
C2: 47u/6V3; C_0805_2012Metric
C3: 100n; C_0603_1608Metric
LED+1, LED+2: SMD50X100
OUT0, OUT1, OUT2, OUT3, OUT4, OUT5, OUT6, OUT7, OUT8, OUT9, OUT10, OUT11, OUT12, OUT13, OUT14, OUT15, OUT15S1: SMD50X100
PAD1: +; SMD80X120
PAD2: -; SMD80X120
PAD3: ST/Rx; SMD80X120
PAD4: TH/Tx; SMD80X120
PAD5: CH3; SMD80X120
PAD6: OUT/ISP; SMD80X120
R1: 2k0=20mA; R_0603_1608Metric
R2, R3, R4, R6: 1k; R_0603_1608Metric
T1: NMOSSOT23; SOT-23
TP1: SWDIO; TP10R
TP2, TP3, TP4, TP5: SWCLK; TP10R
U2: TLC5940PWP; SOP65P640X120-29N
U$1: 3V3; SOT95P300X145-3N
U$2: LPC812; TSSOP-16_4.4x5mm_P0.65mm

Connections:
+3V3: C2.1, C3.2, U2.6 (VPRG), U2.26 (DCPRG), U2.28 (VCC), U$1.2 (VOUT), U$2.12 (VDD)
/BLANK: TP4.TP, U2.2 (BLANK), U$2.15 (PIO0_6/VDDCMP)
/CH3: R6.2, U$2.1 (PIO0_13)
/GSCLK: TP3.TP, U2.25 (GSCLK), U$2.9 (PIO0_1/ACMP_I2/CLKIN/TDI)
/OUT-SWITCHED: T1.3 (G), U$2.10 (PIO0_9/XTALOUT)
/OUT/ISP: R2.2, U$2.2 (PIO0_12)
/SCLK: TP1.TP, U2.4 (SCLK), U$2.6 (PIO0_2/SWDIO/TMS)
/SIN: TP5.TP, U2.5 (SIN), U$2.14 (PIO0_7)
/ST/RX: R3.2, U$2.16 (PIO0_0/ACMP_I1/TDO)
/TH/TX: R4.2, U$2.4 (PIO0_4/WAKEUP/TRST)
/VIN: C1.1, LED+1.1, LED+2.1, PAD1.1, U$1.3 (VIN)
/XLAT: TP2.TP, U2.3 (XLAT), U$2.5 (PIO0_3/SWCLK/TCK)
GND: C1.2, C2.2, C3.1, PAD2.1, R1.1, T1.2 (S), U2.1 (GND), U2.29 (PAD), U$1.1 (GND), U$2.13 (VSS)
unnamed: OUT0.1, U2.7 (OUT_0)
unnamed: OUT1.1, U2.8 (OUT_1)
unnamed: OUT2.1, U2.9 (OUT_2)
unnamed: OUT3.1, U2.10 (OUT_3)
unnamed: OUT4.1, U2.11 (OUT_4)
unnamed: OUT5.1, U2.12 (OUT_5)
unnamed: OUT6.1, U2.13 (OUT_6)
unnamed: OUT7.1, U2.14 (OUT_7)
unnamed: OUT8.1, U2.15 (OUT_8)
unnamed: OUT9.1, U2.16 (OUT_9)
unnamed: OUT10.1, U2.17 (OUT_10)
unnamed: OUT11.1, U2.18 (OUT_11)
unnamed: OUT12.1, U2.19 (OUT_12)
unnamed: OUT13.1, U2.20 (OUT_13)
unnamed: OUT14.1, U2.21 (OUT_14)
unnamed: OUT15.1, U2.22 (OUT_15)
unnamed: OUT15S1.1, T1.1 (D)
unnamed: PAD3.1, R3.1
unnamed: PAD4.1, R4.1
unnamed: PAD5.1, R6.1
unnamed: PAD6.1, R2.1
unnamed: R1.2, U2.27 (IREF)

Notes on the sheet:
Special pins: PIO0_0 (16) ISP UART RX PIO0_4 ( 4) ISP UART TX PIO0_5 ( 3) RESET PIO0_10 ( 8) Open drain PIO0_11 ( 7) Open drain PIO0_2 ( 6) SWDIO PIO0_3 ( 5) SWCLK
Servo in/out
LED driver and outputs
Voltage regulator
Microcontroller
X7R
All resistors 0603
Input voltage range: 4 ... 10V
LDO: Microchip MCP1702 or MCP1703
X5R or X7R
NXP LPC812 ARM Cortex-M0 16K Flash, 4K RAM TSSOP-16
Switched output for light bar or similar
N-Channel MOSFET SOT23 package e.g. NXP PMV16UN
Polymer

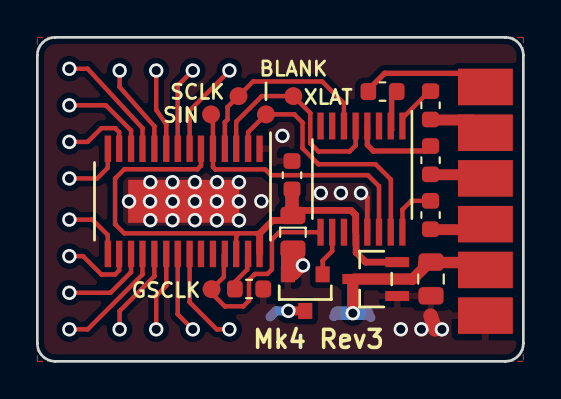
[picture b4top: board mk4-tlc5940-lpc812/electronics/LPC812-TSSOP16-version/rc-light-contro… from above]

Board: 2 copper layers, 27.0 x 18.0 mm, 42 parts (0 on the bottom side), 35 nets.
